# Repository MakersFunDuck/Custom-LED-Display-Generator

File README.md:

# Custom LED Display Generator
A Python-based tool for designing and generating custom LED displays from a single image file.  The goal of this project is to make it easier for electronics hobbyists and makers to create their own custom LED displays without having to manually design the mechanical, graphical, and electronic parts separately.  You define your display and select the required MCU and LED-driving configuration, and the tool generates the files needed to build it.

You may find detailed usage instructions in the video:
https://youtu.be/lEBiFov_C0w

# Installation and Usage

Steps
1. Install Python 3.12

Download from:

Python 3.12 Downloads

https://www.python.org/downloads/release/python-3120/

During install:

check "Add Python to PATH"

Check the active python version
```python -V```

Setup and Run
2. Create a virtual environment

Create a virtual environment named .venv:

```python -m venv .venv```

3. Activate the virtual environment
PowerShell
```.\.venv\Scripts\Activate```

Command Prompt (cmd)
```.\.venv\Scripts\activate.bat```

4. Confirm Python and pip point to the virtual environment
```python -V```
```python -m pip --version```

5. Upgrade pip

Upgrade pip, setuptools, and wheel inside the virtual environment:

```python -m pip install --upgrade pip setuptools wheel```

6. Install dependencies

Install the required Python packages:

```python -m pip install -r requirements.txt```

7. Start the app
```python main.py```

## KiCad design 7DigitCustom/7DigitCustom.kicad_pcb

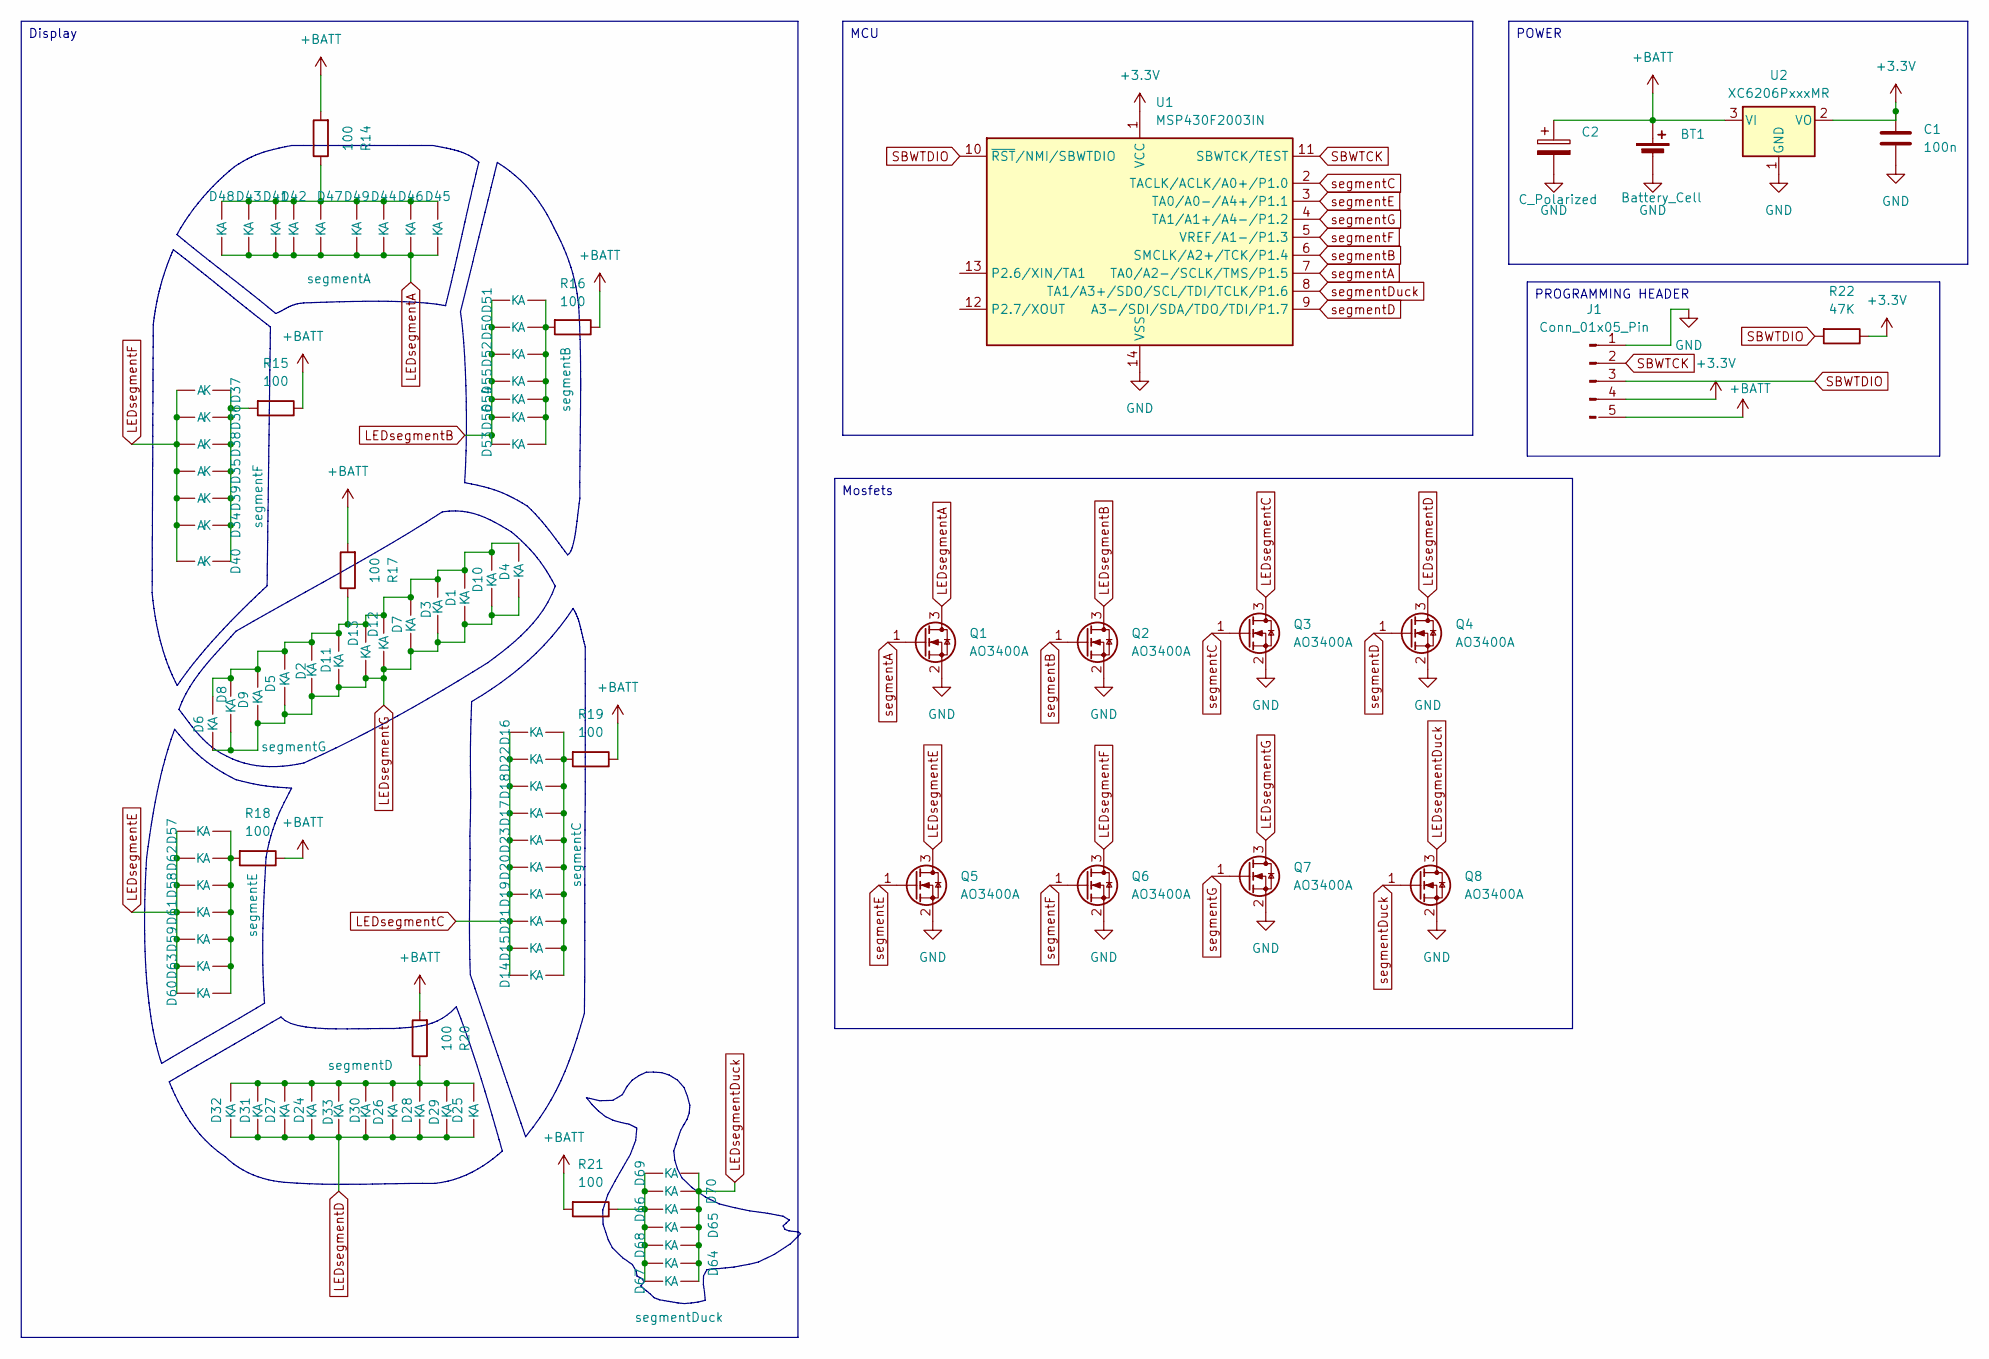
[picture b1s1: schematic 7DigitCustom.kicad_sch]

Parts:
BT1: Battery_Cell; PinHeader_1x02_P2.54mm_Vertical
C1: 100n; C_Radial_D4.0mm_H7.0mm_P1.50mm
C2: C_Polarized; CP_Radial_D10.0mm_P2.50mm
D1, D2, D3, D4, D5, D6, D7, D8, D9, D10, D11, D12, D13: segmentG; LED_0805_2012Metric
D14, D15, D16, D17, D18, D19, D20, D21, D22, D23: segmentC; LED_0805_2012Metric
D24, D25, D26, D27, D28, D29, D30, D31, D32, D33: segmentD; LED_0805_2012Metric
D34, D35, D36, D37, D38, D39, D40: segmentF; LED_0805_2012Metric
D41, D42, D43, D44, D45, D46, D47, D48, D49: segmentA; LED_0805_2012Metric
D50, D51, D52, D53, D54, D55, D56: segmentB; LED_0805_2012Metric
D57, D58, D59, D60, D61, D62, D63: segmentE; LED_0805_2012Metric
D64, D65, D66, D67, D68, D69, D70: segmentDuck; LED_0805_2012Metric
J1: Conn_01x05_Pin; PinHeader_1x05_P2.54mm_Vertical
Q1, Q2, Q3, Q4, Q5, Q6, Q7, Q8: AO3400A; SOT-23
R14, R15, R16, R17, R18, R19, R20, R21: 100; R_Axial_DIN0204_L3.6mm_D1.6mm_P7.62mm_Horizontal
R22: 47K; R_Axial_DIN0204_L3.6mm_D1.6mm_P7.62mm_Horizontal
U1: MSP430F2003IN; DIP-14_W7.62mm
U2: XC6206PxxxMR; SOT-23-3

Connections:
+3.3V: C1.1, J1.4, R22.1, U1.1 (VCC), U2.2 (VO)
+BATT: BT1.1 (+), C2.1, J1.5 (Pin_4), R14.2, R15.1, R16.1, R17.2, R18.1, R19.1, R20.2, R21.2, U2.3 (VI)
GND: BT1.2 (-), C1.2, C2.2, J1.1, Q1.2 (S), Q2.2 (S), Q3.2 (S), Q4.2 (S), Q5.2 (S), Q6.2 (S), Q7.2 (S), Q8.2 (S), U1.14 (VSS), U2.1 (GND)
LEDsegmentA: D41.2 (A), D42.2 (A), D43.2 (A), D44.2 (A), D45.2 (A), D46.2 (A), D47.2 (A), D48.2 (A), D49.2 (A), Q1.3 (D)
LEDsegmentB: D50.2 (A), D51.2 (A), D52.2 (A), D53.2 (A), D54.2 (A), D55.2 (A), D56.2 (A), Q2.3 (D)
LEDsegmentC: D14.2 (A), D15.2 (A), D16.2 (A), D17.2 (A), D18.2 (A), D19.2 (A), D20.2 (A), D21.2 (A), D22.2 (A), D23.2 (A), Q3.3 (D)
LEDsegmentD: D24.2 (A), D25.2 (A), D26.2 (A), D27.2 (A), D28.2 (A), D29.2 (A), D30.2 (A), D31.2 (A), D32.2 (A), D33.2 (A), Q4.3 (D)
LEDsegmentDuck: D64.1 (K), D65.1 (K), D66.1 (K), D67.1 (K), D68.1 (K), D69.1 (K), D70.1 (K), Q8.3 (D)
LEDsegmentE: D57.2 (A), D58.2 (A), D59.2 (A), D60.2 (A), D61.2 (A), D62.2 (A), D63.2 (A), Q5.3 (D)
LEDsegmentF: D34.1 (K), D35.1 (K), D36.1 (K), D37.1 (K), D38.1 (K), D39.1 (K), D40.1 (K), Q6.3 (D)
LEDsegmentG: D1.2 (A), D2.2 (A), D3.2 (A), D4.2 (A), D5.2 (A), D6.2 (A), D7.2 (A), D8.2 (A), D9.2 (A), D10.2 (A), D11.2 (A), D12.2 (A), D13.2 (A), Q7.3 (D)
unnamed: D1.1 (K), D2.1 (K), D3.1 (K), D4.1 (K), D5.1 (K), D6.1 (K), D7.1 (K), D8.1 (K), D9.1 (K), D10.1 (K), D11.1 (K), D12.1 (K), D13.1 (K), R17.1
unnamed: D14.1 (K), D15.1 (K), D16.1 (K), D17.1 (K), D18.1 (K), D19.1 (K), D20.1 (K), D21.1 (K), D22.1 (K), D23.1 (K), R19.2
unnamed: D24.1 (K), D25.1 (K), D26.1 (K), D27.1 (K), D28.1 (K), D29.1 (K), D30.1 (K), D31.1 (K), D32.1 (K), D33.1 (K), R20.1
unnamed: D34.2 (A), D35.2 (A), D36.2 (A), D37.2 (A), D38.2 (A), D39.2 (A), D40.2 (A), R15.2
unnamed: D41.1 (K), D42.1 (K), D43.1 (K), D44.1 (K), D45.1 (K), D46.1 (K), D47.1 (K), D48.1 (K), D49.1 (K), R14.1
unnamed: D50.1 (K), D51.1 (K), D52.1 (K), D53.1 (K), D54.1 (K), D55.1 (K), D56.1 (K), R16.2
unnamed: D57.1 (K), D58.1 (K), D59.1 (K), D60.1 (K), D61.1 (K), D62.1 (K), D63.1 (K), R18.2
unnamed: D64.2 (A), D65.2 (A), D66.2 (A), D67.2 (A), D68.2 (A), D69.2 (A), D70.2 (A), R21.1
SBWTCK: J1.2, U1.11 (SBWTCK/TEST)
SBWTDIO: J1.3, R22.2, U1.10 (~RST/NMI/SBWTDIO)
segmentA: Q1.1 (G), U1.7 (TA0/A2-/SCLK/TMS/P1.5)
segmentB: Q2.1 (G), U1.6 (SMCLK/A2+/TCK/P1.4)
segmentC: Q3.1 (G), U1.2 (TACLK/ACLK/A0+/P1.0)
segmentD: Q4.1 (G), U1.9 (A3-/SDI/SDA/TDO/TDI/P1.7)
segmentDuck: Q8.1 (G), U1.8 (TA1/A3+/SDO/SCL/TDI/TCLK/P1.6)
segmentE: Q5.1 (G), U1.3 (TA0/A0-/A4+/P1.1)
segmentF: Q6.1 (G), U1.5 (VREF/A1-/P1.3)
segmentG: Q7.1 (G), U1.4 (TA1/A1+/A4-/P1.2)

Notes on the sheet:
Display
PROGRAMMING HEADER
MCU
Mosfets
POWER

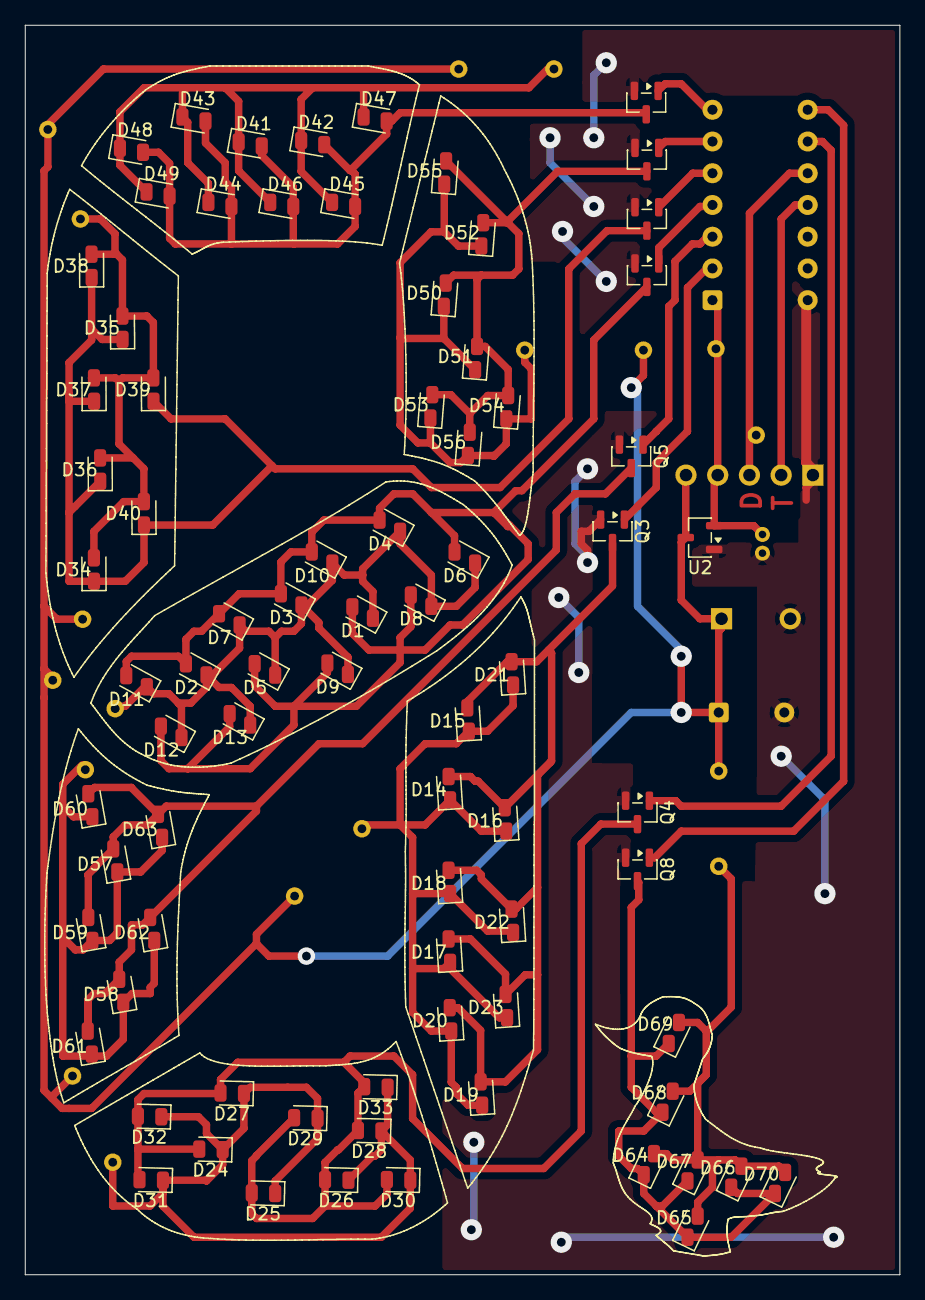
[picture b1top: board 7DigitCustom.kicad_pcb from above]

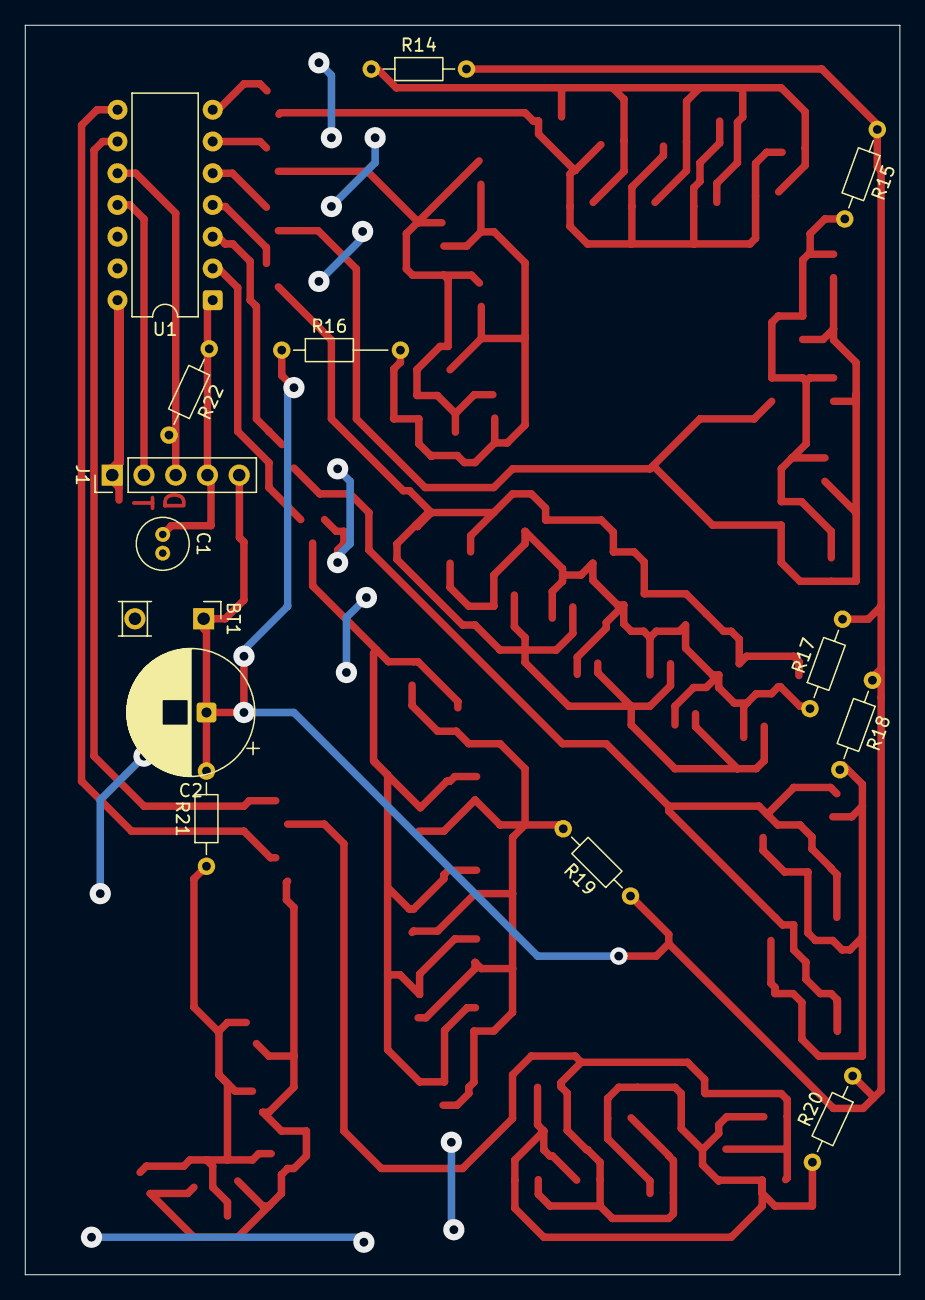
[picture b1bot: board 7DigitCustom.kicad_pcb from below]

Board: 2 copper layers, 70.0 x 100.0 mm, 93 parts (14 on the bottom side), 29 nets.
